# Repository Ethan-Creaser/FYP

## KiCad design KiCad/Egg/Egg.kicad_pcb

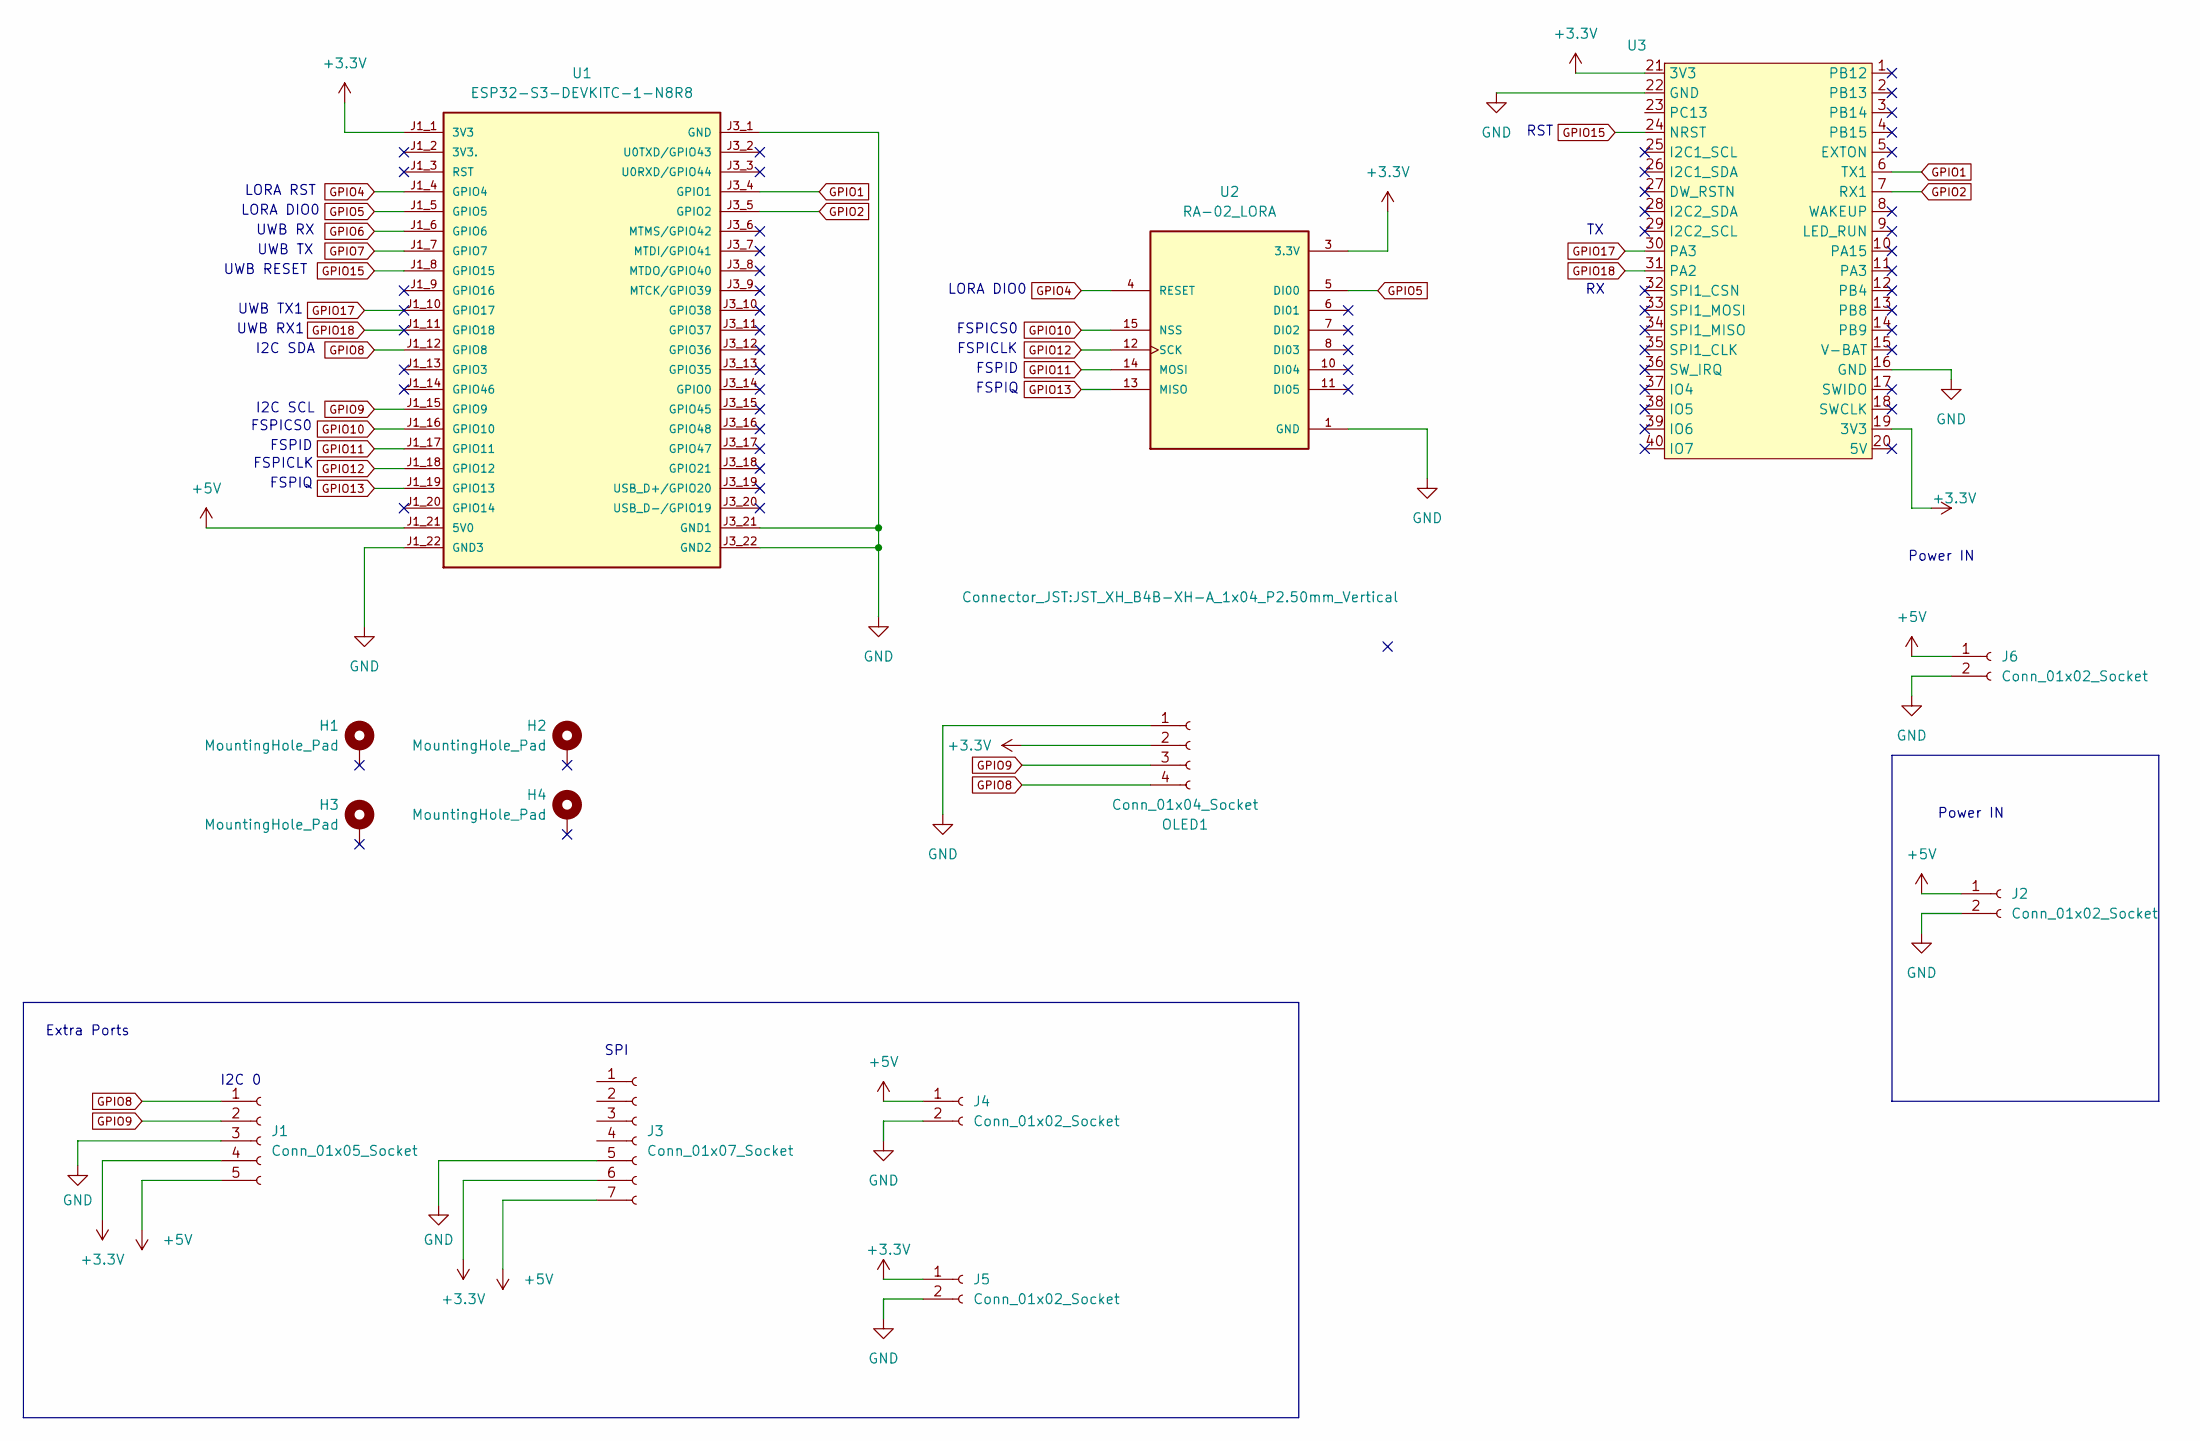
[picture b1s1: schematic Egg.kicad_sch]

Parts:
H1, H2, H3, H4: MountingHole_Pad; MountingHole_3.2mm_M3_ISO14580_Pad
J1: Conn_01x05_Socket; JST_XH_B5B-XH-A_1x05_P2.50mm_Vertical
J2: Conn_01x02_Socket; JST_PH_B2B-PH-K_1x02_P2.00mm_Vertical
J3: Conn_01x07_Socket; JST_XH_B7B-XH-A_1x07_P2.50mm_Vertical
J4, J5, J6: Conn_01x02_Socket; JST_XH_B2B-XH-A_1x02_P2.50mm_Vertical
OLED1: Conn_01x04_Socket; JST_XH_B4B-XH-A_1x04_P2.50mm_Vertical
U1: ESP32-S3-DEVKITC-1-N8R8
U2: RA-02_LORA; Lora_Dev_Board; PARTREV 2018/03/02
U3: UWB_Female_Headers

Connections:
+3.3V: J1.4, J3.6, J5.1, OLED1.2, U1.J1_1 (3V3), U2.3 (3.3V), U3.19 (3V3), U3.21 (3V3)
+5V: J1.5, J2.1, J3.7, J4.1, J6.1, U1.J1_21 (5V0)
GND: J1.3, J2.2, J3.5, J4.2, J5.2, J6.2, OLED1.1, U1.J1_22 (GND3), U1.J3_1 (GND), U1.J3_21 (GND1), U1.J3_22 (GND2), U2.1 (GND), U2.2 (GND), U2.9 (GND), U2.16 (GND), U3.16 (GND), U3.22 (GND)
GPIO1: U1.J3_4 (GPIO1), U3.6 (TX1)
GPIO2: U1.J3_5 (GPIO2), U3.7 (RX1)
GPIO4: U1.J1_4 (GPIO4), U2.4 (RESET)
GPIO5: U1.J1_5 (GPIO5), U2.5 (DI00)
GPIO6: U1.J1_6 (GPIO6)
GPIO7: U1.J1_7 (GPIO7)
GPIO8: J1.1, OLED1.4, U1.J1_12 (GPIO8)
GPIO9: J1.2, OLED1.3, U1.J1_15 (GPIO9)
GPIO10: U1.J1_16 (GPIO10), U2.15 (NSS)
GPIO11: U1.J1_17 (GPIO11), U2.14 (MOSI)
GPIO12: U1.J1_18 (GPIO12), U2.12 (SCK)
GPIO13: U1.J1_19 (GPIO13), U2.13 (MISO)
GPIO15: U1.J1_8 (GPIO15), U3.24 (NRST)
GPIO17: U1.J1_10 (GPIO17), U3.30 (PA3)
GPIO18: U1.J1_11 (GPIO18), U3.31 (PA2)

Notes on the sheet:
I2C 0
RST
LORA RST
FSPID
FSPICLK
I2C SDA
Power IN
UWB RX1
UWB TX1
UWB TX
FSPICS0
UWB RESET
SPI
UWB RX
Extra Ports
LORA DIO0
FSPIQ
I2C SCL

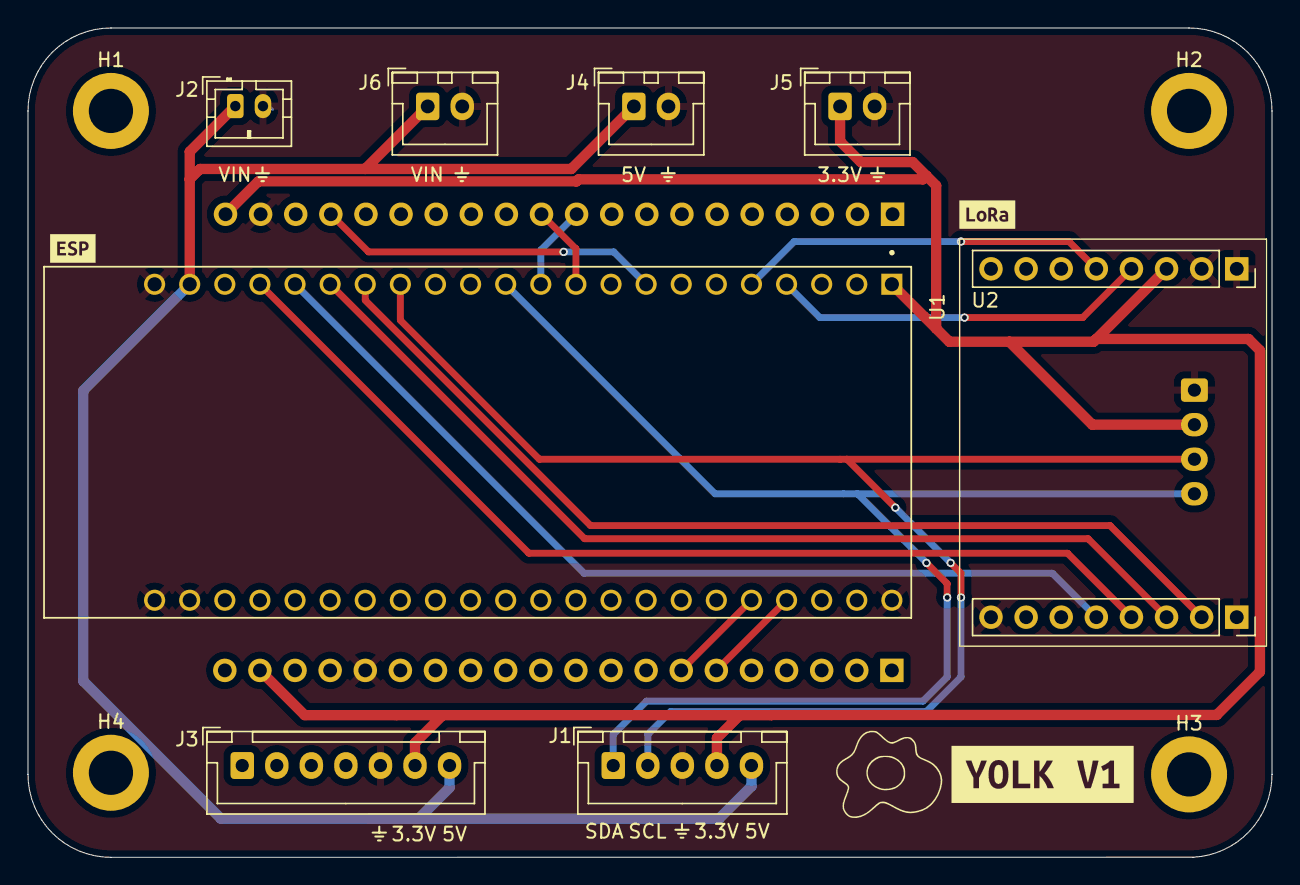
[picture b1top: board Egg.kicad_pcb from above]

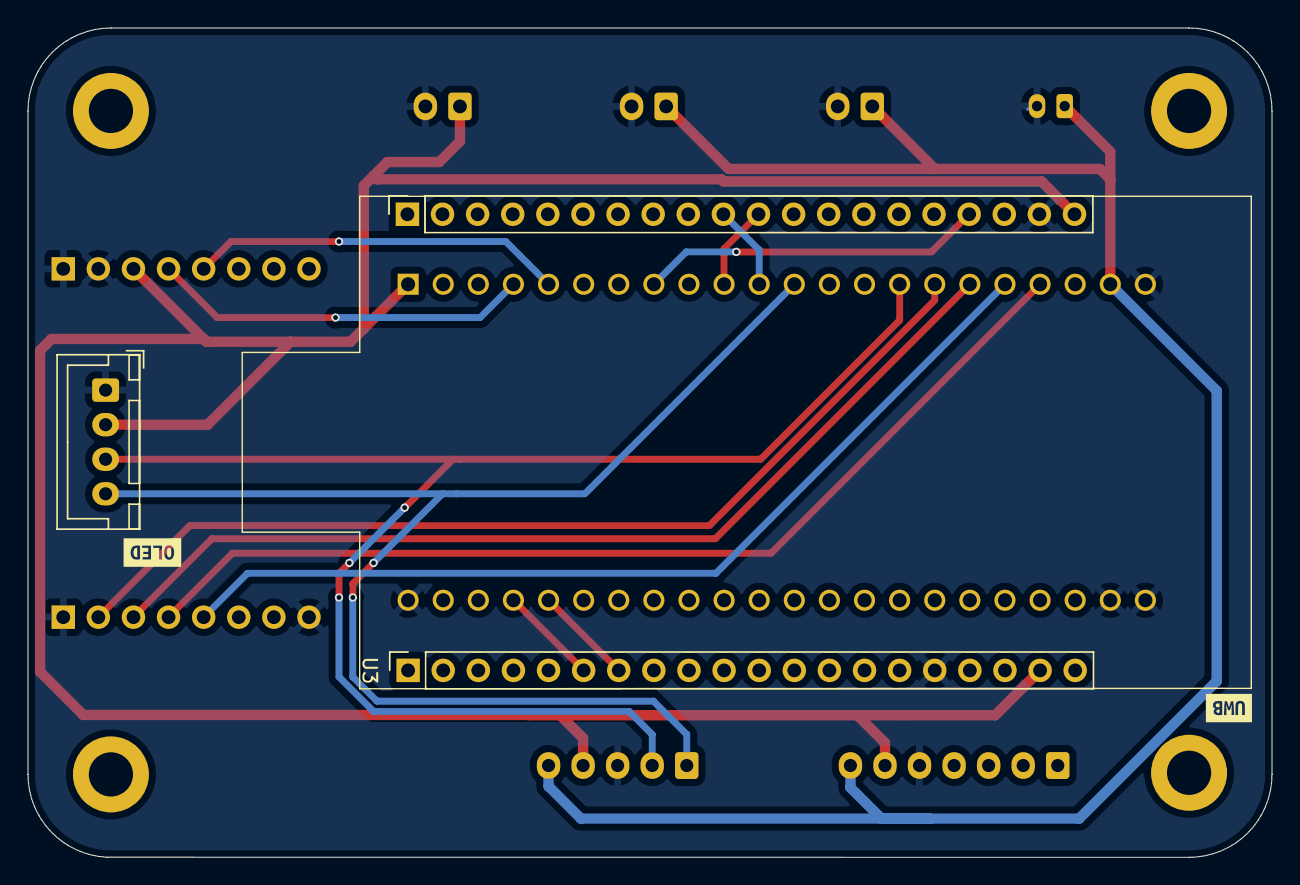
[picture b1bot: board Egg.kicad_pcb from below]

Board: 4 copper layers, 90.0 x 60.0 mm, 19 parts (4 on the bottom side), 16 nets.

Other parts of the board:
kibuzzard-69B7B320: G***; kibuzzard-69B7B320
kibuzzard-69BA5F59: G***; kibuzzard-69BA5F59
kibuzzard-69BA57B0: G***; kibuzzard-69BA57B0
kibuzzard-69BA525D: G***; kibuzzard-69BA525D
kibuzzard-69BA529B: G***; kibuzzard-69BA529B

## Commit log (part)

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2025-10-16 lora test.py
2025-10-21 add: second type of lora code
2025-10-21 feature(cpp): blink external LED test
2025-10-21 feature(python): ulora code
2025-10-21 feature: add blink led to ulora
2025-10-21 Reorganised Files
2025-10-23 tweaks
2026-02-02 add: KiCad folder + ESP/LoRa schematics
2026-02-02 Add: RGB cycle test for ESP32 S3 via Micropython
2026-02-02 Add: filetree organisation for pymakr
2026-02-02 feat(lora): add lora send/receive scripts to micropython
    add Lora sender and receiver scripts to micropython
    configure STM pins in lora code
2026-02-02 fix(lora): comment out old LED code
    comment out old PiCO LED code
2026-02-05 Update main.py
    Added lora code
2026-02-05 feat(uLora): add send and receive folders
    add send and receive folders with respective boot.py and main.py to run send and receive when powered up
2026-02-09 Added ECAD feature: Mounting Holes, PCB outline and UWB footprint
2026-02-15 Create oled.py to test OLED screen
2026-02-24 create bu03 configuration file
    this file assigns ID and role to the boards to make them start localisign
2026-02-24 create proposed file structure
    I've added my proposed file structure for all the egg's files
2026-03-01 Add documentation for AT commands and uwb
2026-03-01 Update uwb documentation with tutorial
2026-03-11 Add Feature
    Two side PCB
2026-03-11 chore(schematic): Change UWB pinout
    NEEDS UPDATING WITH PA2 AND PA3 PINOUT
    change UWB pins to UART on ESP
2026-03-11 idk
    idk
2026-03-11 Restructure
    added a micropythpon pico project
2026-03-11 add feature
    added classes for oled and lora and updated main to reflect
2026-03-11 add feature
    added reading functions
2026-03-11 add uwb configuration debug file
2026-03-11 add feature
    add UWB read data function to main
2026-03-12 fix bug:
    ESP was stuck in lora initialise loop if lora wasn't connected properly
2026-03-12 fix bug
2026-03-16 add feature
    add second UART line for configureing UART
2026-03-18 New Egg Folder
2026-03-19 production pcb
2026-04-15 Create Nodes_0
2026-04-15 Node_All
    All nodes except the gateway. update config file for each node with id number
2026-04-15 server
    Server file for the uwb display
2026-04-15 lora.py
    Debugs
    1) changed & to == in recieved packet()
    2) removing MODE_RX_SINGLE so that radio stays in continous rx mode
    3) the driver was using gpio15 as a led which was clashing with that pin being our reset pin so removed that
2026-04-17 Delete Feature: Kikad Files
    KICAD-delete
2026-04-19 create polling loop and assc files
    - implemented mvp polling loop architecture
    - currently just mesh testing (heartbeat, sensor, neighbour sensing)
    - yet to implement uwb ranging
2026-04-21 fix: cleaned up print outputs
    - made prettier print statements
    - more readable
    - seems to be slower need to ivestigate
2026-04-21 add: code documentation
    - added function headers to node.py and timers.py
2026-04-21 add node_logger.py
    - removing this from node.py for readability
2026-04-21 add boot_id for packets
    - added a pseudo random boot id on startup to avoid reanimation issue
2026-04-22 Delete Feature:
    Removing old code
2026-04-23 add LED neighbour status
2026-04-24 add feature: general expection handleing
2026-04-28 Create placeholder
2026-04-28 Delete Node_All
    redundant
2026-04-28 Delete Nodes_0
    redundant
2026-04-28 Delete server
    redundant
2026-04-28 Delete Code directory
    redundant
2026-04-28 add feature: image send
2026-04-29 add localisatoin integration
    - attempted to integrate uwb from ashnoors branch
    - need to integrate the visualiser
2026-04-29 update config file
    just changes the config file a bit for testing
2026-04-29 add: image bins
2026-04-29 fix_bug: blueooth caused crash and reset on initialisation
2026-05-02 Add hardware adapter, minimal config, and node hardware glue
2026-05-02 Add minimal main.py to start node and hardware polling
2026-05-02 Add hw_runner.py test script for on-device send/ACK validation
2026-05-02 MicroPython compatibility: remove __future__ imports and dataclass usage
2026-05-02 Make code MicroPython-friendly: remove typing imports and annotations
2026-05-02 hw_runner: default peer target for nodes 1/2 and add jitter before send
2026-05-03 add hardware test files
    - so much has changed whoops but added lora test files
    - it uses CAD/LBT as collision avoidance now
2026-05-03 minor syntax change
2026-05-03 fix: removed all the type hints
2026-05-03 change packet scheme
    - simplified to 4 packet types
    - added sender id to packet header for multi hop comms
    - fixed beacon reset timer
2026-05-03 add feature: UWB role assingment over lora
2026-05-03 add feature: send data after role reassign
2026-05-06 add updates routing and packet scheme
    - bunch of edits to meshing timing, packet scheme, etc
2026-05-06 add feature: automated role assignment and data collection
2026-05-12 change: toplogy on identity bin now
2026-05-13 add feature: multi-hop localisation fixes
    RREP removed from outstanding RREPs were being retried by egg 8 while egg 7 was trying to forward the config command — half-duplex collision meant egg 8 never received it
    Relay re-forwards on dup if pending_forward unACKed Egg 7 records (src, seq) in _seen on first transmission; if egg 8 misses it and egg 6 retries, egg 7 was silently dropping the retry as a dup inste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
    pending_forwards timestamped and expired Relay entries had no TTL — if the ACK chain broke the entry stayed forever, leaking memory on MicroPython
    RREQ failure clears outstanding entry On RREQ exhaustion the packet was dropped from _pending_data but remained in ou
2026-05-13 commit worktrees
2026-05-13 fix: mapping function
2026-05-17 automated topology update
2026-05-17 add: beacon disable
2026-05-17 add feature: range_test, beacon reasign
2026-05-19 add feature: mesh testing scripts
2026-05-19 add feature: topology check before ping
2026-05-21 testing_mesh updates
2026-05-21 fix test 1a
    - major bug fix for rrep delivery across more 3 hops
    - other fixes
2026-05-22 Create bu03_send_at.py
    make script to send AT commands to UWB through ESP micropython
2026-05-22 fix: edit rreq backoff timing
    - added topology name to csv name
    - added random rreq bcast backoff timing to reduce collision
